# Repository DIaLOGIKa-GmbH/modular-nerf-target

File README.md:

# Nodular Nerf Target

A hex-based modular system to build custom nerf gun targets

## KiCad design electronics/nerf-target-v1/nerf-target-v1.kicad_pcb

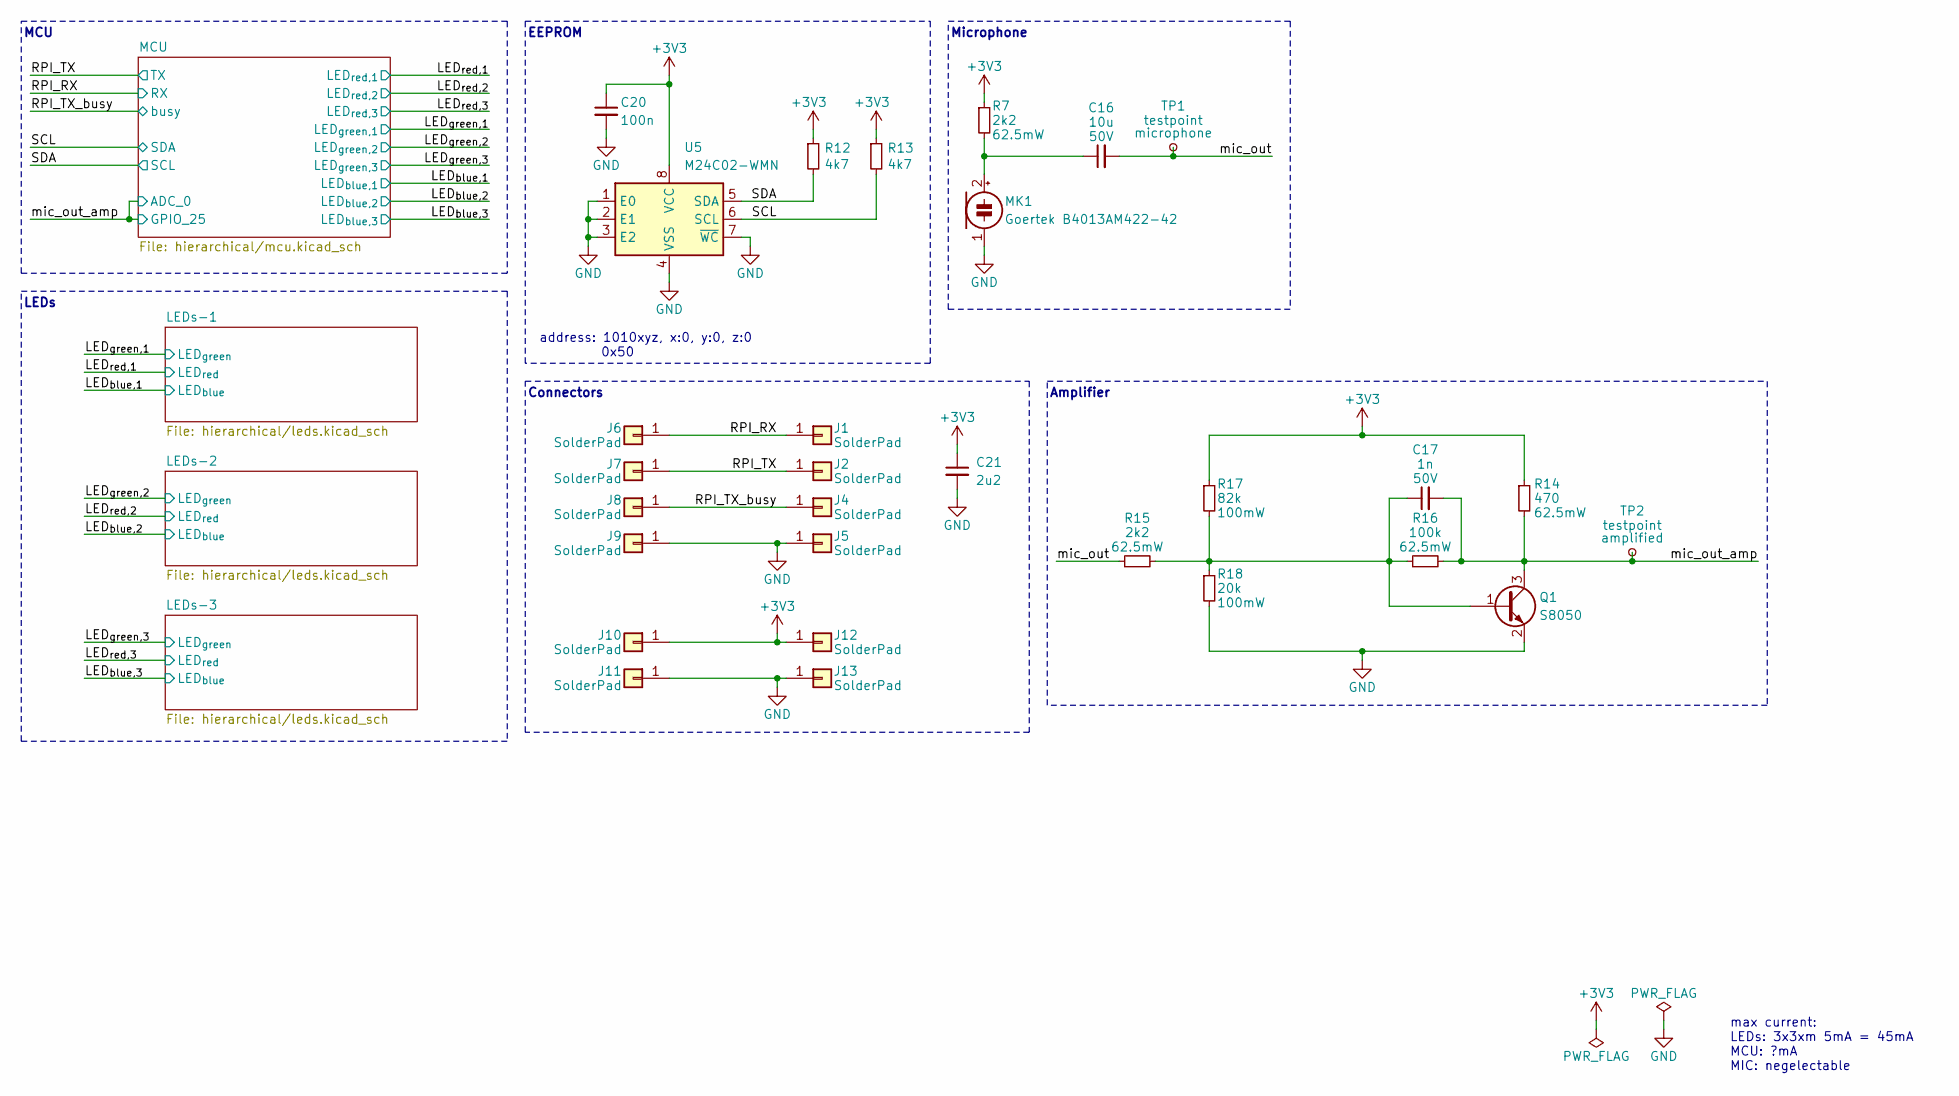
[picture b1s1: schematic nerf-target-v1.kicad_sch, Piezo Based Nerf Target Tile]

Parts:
C16: 10u; C_0805_2012Metric; Voltage 50V; LCSC Part # C440198
C17: 1n; C_0805_2012Metric; Voltage 50V; LCSC Part # C46653
C20: 100n; C_0402_1005Metric; LCSC Part # C1525
C21: 2u2; C_0603_1608Metric; JLC Part # C28323
J1, J2, J4, J5, J6, J7, J8, J9, J10, J11, J12, J13: SolderPad; solder_pad_1.2x2.5mm
MK1: Goertek B4013AM422-42; B4013AM422-42; LCSC Part # C233793
Q1: S8050; SOT-23; LCSC Part # C2146
R7, R15: 2k2; R_0402_1005Metric; LCSC Part # C25879
R12, R13: 4k7; R_0603_1608Metric; LCSC Part # C23162
R14: 470; R_0402_1005Metric; LCSC Part # C25117
R16: 100k; R_0603_1608Metric; LCSC Part # C25741
R17: 82k; R_0603_1608Metric; LCSC Part # C23254
R18: 20k; R_0603_1608Metric; LCSC Part # C4184
TP1, TP2: testpoint; TestPoint_Pad_D2.0mm
U5: M24C02-WMN; SOIC-8_3.9x4.9mm_P1.27mm; LCSC Part # C7562

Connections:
+3V3: C20.1, C21.1, J10.1, J12.1, R7.1, R12.1, R13.1, R14.1, R17.1, U5.8 (VCC); also elsewhere on the board
/RPI_RX: J1.1, J6.1; also elsewhere on the board
/RPI_TX: J2.1, J7.1; also elsewhere on the board
/RPI_TX_busy: J4.1, J8.1; also elsewhere on the board
/SCL: R13.2, U5.6 (SCL); also elsewhere on the board
/SDA: R12.2, U5.5 (SDA); also elsewhere on the board
/mic_out: C16.2, R15.1, TP1.1
/mic_out_amp: C17.2, Q1.3 (C), R14.2, R16.2, TP2.1; also elsewhere on the board
GND: C20.2, C21.2, J5.1, J9.1, J11.1, J13.1, MK1.1 (-), Q1.2 (E), R18.2, U5.1 (E0), U5.2 (E1), U5.3 (E2), U5.4 (VSS), U5.7 (~WC); also elsewhere on the board
unnamed: C16.1, MK1.2 (+), R7.2
unnamed: C17.1, Q1.1 (B), R15.2, R16.1, R17.2, R18.1

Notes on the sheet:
max current: LEDs: 3x3xm 5mA = 45mA MCU: ?mA MIC: negelectable
Microphone
Amplifier
MCU
Connectors
EEPROM
address: 1010xyz, x:0, y:0, z:0 0x50
LEDs

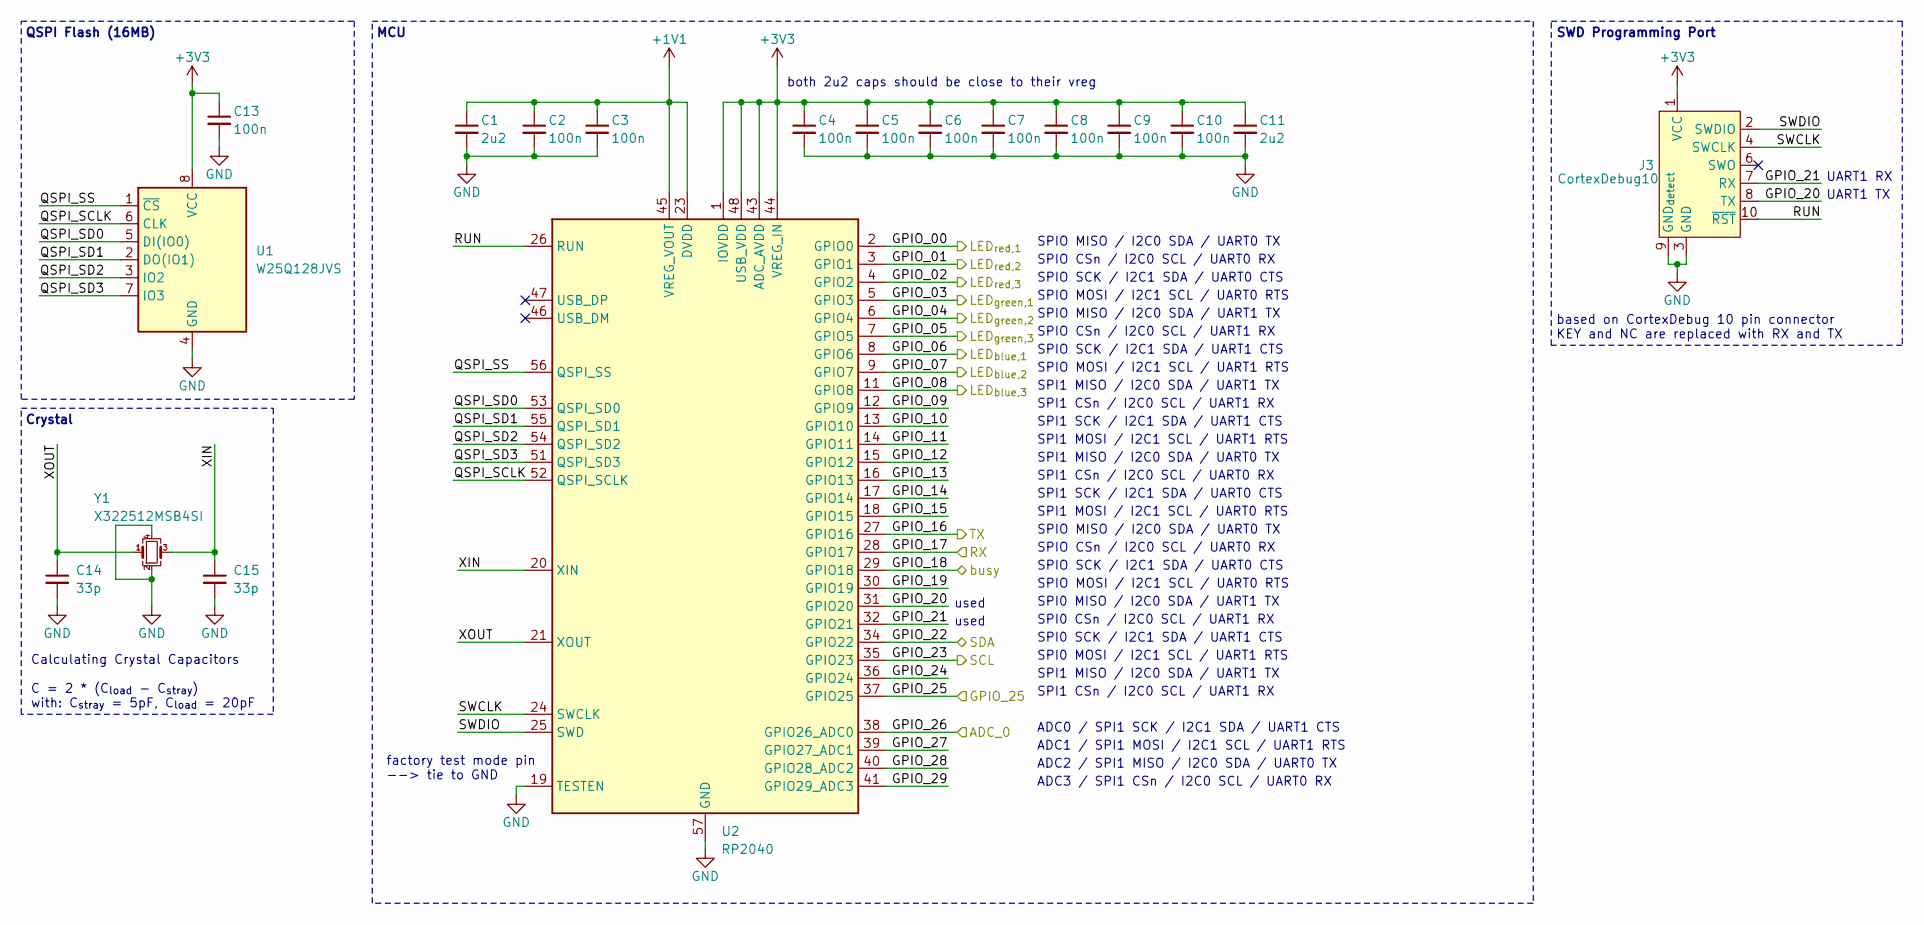
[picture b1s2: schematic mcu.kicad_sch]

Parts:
C1, C11: 2u2; C_0603_1608Metric; LCSC Part # C23630
C2, C3, C4, C5, C6, C7, C8, C9, C10, C13: 100n; C_0402_1005Metric; LCSC Part # C1525
C14, C15: 33p; C_0402_1005Metric; LCSC Part # C1562
J3: CortexDebug10; FTSH-105-01-F-DV-K; LCSC Part # C3975188
U1: W25Q128JVS; SOIC-8_5.275x5.275mm_P1.27mm; LCSC Part # C97521
U2: RP2040; QFN-56-1EP_7x7mm_P0.4mm_EP3.2x3.2mm; LCSC Part # C2040
Y1: X322512MSB4SI; Crystal_SMD_3225-4Pin_3.2x2.5mm; LCSC Part # C9002

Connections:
+1V1: C1.1, C2.1, C3.1, U2.23 (DVDD), U2.45 (VREG_VOUT), U2.50 (DVDD)
+3V3: C4.1, C5.1, C6.1, C7.1, C8.1, C9.1, C10.1, C11.1, C13.1, J3.1 (VCC), U1.8 (VCC), U2.1 (IOVDD), U2.10 (IOVDD), U2.22 (IOVDD), U2.33 (IOVDD), U2.42 (IOVDD), U2.43 (ADC_AVDD), U2.44 (VREG_IN), U2.48 (USB_VDD), U2.49 (IOVDD); also elsewhere on the board
/LED_{blue,1}: U2.8 (GPIO6); also elsewhere on the board
/LED_{blue,2}: U2.9 (GPIO7); also elsewhere on the board
/LED_{blue,3}: U2.11 (GPIO8); also elsewhere on the board
/LED_{green,1}: U2.5 (GPIO3); also elsewhere on the board
/LED_{green,2}: U2.6 (GPIO4); also elsewhere on the board
/LED_{green,3}: U2.7 (GPIO5); also elsewhere on the board
/LED_{red,1}: U2.2 (GPIO0); also elsewhere on the board
/LED_{red,2}: U2.3 (GPIO1); also elsewhere on the board
/LED_{red,3}: U2.4 (GPIO2); also elsewhere on the board
/MCU/GPIO_09: U2.12 (GPIO9)
/MCU/GPIO_10: U2.13 (GPIO10)
/MCU/GPIO_11: U2.14 (GPIO11)
/MCU/GPIO_12: U2.15 (GPIO12)
/MCU/GPIO_13: U2.16 (GPIO13)
/MCU/GPIO_14: U2.17 (GPIO14)
/MCU/GPIO_15: U2.18 (GPIO15)
/MCU/GPIO_19: U2.30 (GPIO19)
/MCU/GPIO_20: J3.8 (TX), U2.31 (GPIO20)
/MCU/GPIO_21: J3.7 (RX), U2.32 (GPIO21)
/MCU/GPIO_24: U2.36 (GPIO24)
/MCU/GPIO_27: U2.39 (GPIO27_ADC1)
/MCU/GPIO_28: U2.40 (GPIO28_ADC2)
/MCU/GPIO_29: U2.41 (GPIO29_ADC3)
/MCU/QSPI_SCLK: U1.6 (CLK), U2.52 (QSPI_SCLK)
/MCU/QSPI_SD0: U1.5 (DI(IO0)), U2.53 (QSPI_SD0)
/MCU/QSPI_SD1: U1.2 (DO(IO1)), U2.55 (QSPI_SD1)
/MCU/QSPI_SD2: U1.3 (IO2), U2.54 (QSPI_SD2)
/MCU/QSPI_SD3: U1.7 (IO3), U2.51 (QSPI_SD3)
/MCU/QSPI_SS: U1.1 (~CS), U2.56 (QSPI_SS)
/MCU/RUN: J3.10 (~RST), U2.26 (RUN)
/MCU/SWCLK: J3.4 (SWCLK), U2.24 (SWCLK)
/MCU/SWDIO: J3.2 (SWDIO), U2.25 (SWD)
/MCU/XIN: C15.1, U2.20 (XIN), Y1.3
/MCU/XOUT: C14.1, U2.21 (XOUT), Y1.1
/RPI_RX: U2.28 (GPIO17); also elsewhere on the board
/RPI_TX: U2.27 (GPIO16); also elsewhere on the board
/RPI_TX_busy: U2.29 (GPIO18); also elsewhere on the board
/SCL: U2.34 (GPIO22); also elsewhere on the board
/SDA: U2.35 (GPIO23); also elsewhere on the board
/mic_out_amp: U2.37 (GPIO25), U2.38 (GPIO26_ADC0); also elsewhere on the board
GND: C1.2, C2.2, C3.2, C4.2, C5.2, C6.2, C7.2, C8.2, C9.2, C10.2, C11.2, C13.2, C14.2, C15.2, J3.3 (GND), J3.5 (GND), J3.9 (GND_{detect}), U1.4 (GND), U2.19 (TESTEN), U2.57 (GND), Y1.2, Y1.4; also elsewhere on the board

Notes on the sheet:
SPI1 SCK / I2C1 SDA / UART0 CTS
SPIO CSn / I2C0 SCL / UART1 RX
SPI1 MISO / I2C0 SDA / UART1 TX
SPI1 CSn / I2C0 SCL / UART0 RX
SPI0 SCK / I2C1 SDA / UART1 CTS
SPI0 MOSI / I2C1 SCL / UART1 RTS
SPIO MOSI / I2C1 SCL / UART1 RTS
SPIO CSn / I2C0 SCL / UART0 RX
SPI1 SCK / I2C1 SDA / UART1 CTS
SPIO MOSI / I2C1 SCL / UART0 RTS
SPIO SCK / I2C1 SDA / UART0 CTS
ADC3 / SPI1 CSn / I2C0 SCL / UART0 RX
SPI1 MOSI / I2C1 SCL / UART0 RTS
SPI1 CSn / I2C0 SCL / UART1 RX
ADC0 / SPI1 SCK / I2C1 SDA / UART1 CTS
SPI0 MISO / I2C0 SDA / UART1 TX
based on CortexDebug 10 pin connector KEY and NC are replaced with RX and TX
UART1 RX
SWD Programming Port
SPI1 MOSI / I2C1 SCL / UART1 RTS
Crystal
SPIO SCK / I2C1 SDA / UART1 CTS
SPI1 MISO / I2C0 SDA / UART0 TX
Calculating Crystal Capacitors C = 2 * (C_{load} - C_{stray}) with: C_{stray} = 5pF, C_{load} = 20pF
SPIO MISO / I2C0 SDA / UART0 TX
used
SPIO MISO / I2C0 SDA / UART1 TX
factory test mode pin --> tie to GND
QSPI Flash (16MB)
both 2u2 caps should be close to their vreg
UART1 TX
ADC2 / SPI1 MISO / I2C0 SDA / UART0 TX
SPI0 CSn / I2C0 SCL / UART1 RX
MCU
ADC1 / SPI1 MOSI / I2C1 SCL / UART1 RTS

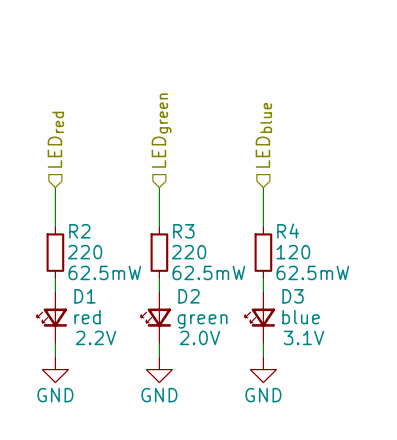
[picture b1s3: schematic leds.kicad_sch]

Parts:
D1: red; LED_0603_1608Metric; Voltage 2.2V; LCSC Part # C2286
D2: green; LED_0603_1608Metric; Voltage 2.0V; LCSC Part # C84264
D3: blue; LED_0603_1608Metric; Voltage 3.1V; LCSC Part # C965807
R2, R3: 220; R_0402_1005Metric; LCSC Part # C25091
R4: 120; R_0402_1005Metric; LCSC Part # C25079

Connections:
/LED_{blue,1}: R4.1; also elsewhere on the board
/LED_{green,1}: R3.1; also elsewhere on the board
/LED_{red,1}: R2.1; also elsewhere on the board
GND: D1.1 (K), D2.1 (K), D3.1 (K); also elsewhere on the board
unnamed: D1.2 (A), R2.2
unnamed: D2.2 (A), R3.2
unnamed: D3.2 (A), R4.2

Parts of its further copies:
D4, D7: red; LED_0603_1608Metric; Voltage 2.2V; LCSC Part # C2286
D5, D8: green; LED_0603_1608Metric; Voltage 2.0V; LCSC Part # C84264
D6, D9: blue; LED_0603_1608Metric; Voltage 3.1V; LCSC Part # C965807
R5, R6, R9, R10: 220; R_0402_1005Metric; LCSC Part # C25091
R8, R11: 120; R_0402_1005Metric; LCSC Part # C25079

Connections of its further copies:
/LED_{blue,2}: R8.1; also elsewhere on the board
/LED_{blue,3}: R11.1; also elsewhere on the board
/LED_{green,2}: R6.1; also elsewhere on the board
/LED_{green,3}: R10.1; also elsewhere on the board
/LED_{red,2}: R5.1; also elsewhere on the board
/LED_{red,3}: R9.1; also elsewhere on the board
GND: D4.1 (K), D5.1 (K), D6.1 (K), D7.1 (K), D8.1 (K), D9.1 (K); also elsewhere on the board
unnamed: D4.2 (A), R5.2
unnamed: D5.2 (A), R6.2
unnamed: D6.2 (A), R8.2
unnamed: D7.2 (A), R9.2
unnamed: D8.2 (A), R10.2
unnamed: D9.2 (A), R11.2

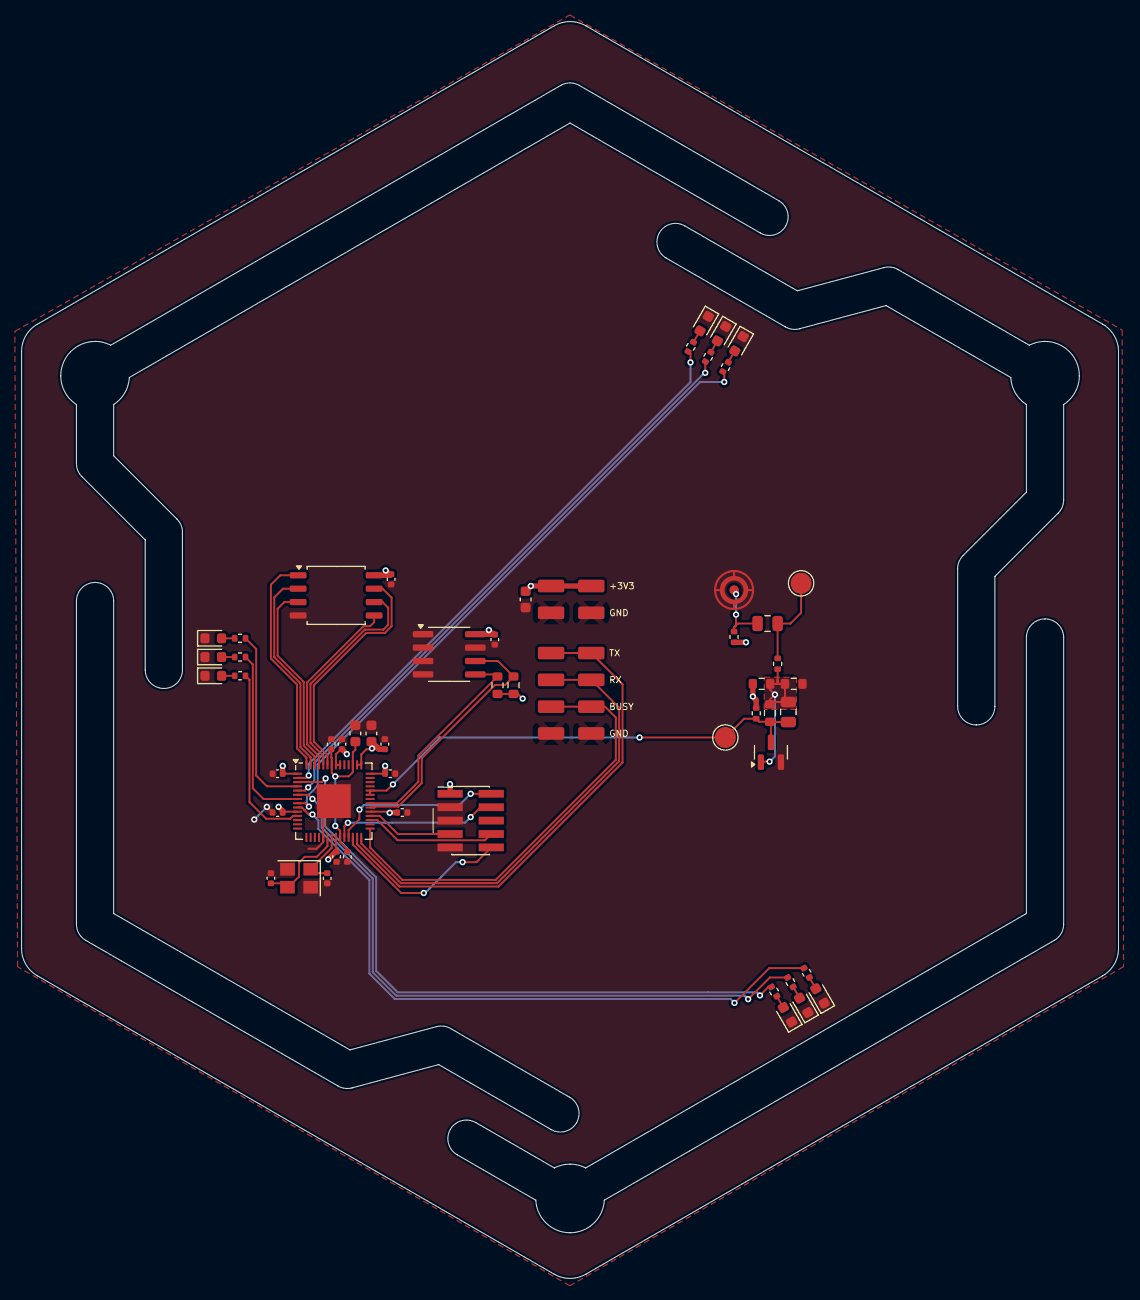
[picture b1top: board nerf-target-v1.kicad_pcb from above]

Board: 2 copper layers, 103.9 x 119.1 mm, 65 parts (0 on the bottom side), 43 nets.

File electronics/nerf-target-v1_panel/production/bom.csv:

Designator,Footprint,Quantity,Value,LCSC Part #
"C1_4, C1_3, C1_2, C1, C11_4, C11_3, C11_2, C11, C21_4, C21_3, C21_2, C21",0603,12,2u2,C23630
"C10_4, C10_3, C10_2, C10, C13_4, C13_3, C13_2, C13, C2_4, C2_3, C2_2, C2, C20_4, C20_3, C20_2, C20, C3_4, C3_3, C3_2, C3, C4_4, C4_3, C4_2, C4, C5_4, C5_3, C5_2, C5, C6_4, C6_3, C6_2, C6, C7_4, C7_3, C7_2, C7, C8_4, C8_3, C8_2, C8, C9_4, C9_3, C9_2, C9",0402,44,100n,C1525
"C14_4, C14_3, C14_2, C14, C15_4, C15_3, C15_2, C15",0402,8,33p,C1562
"C16_4, C16_3, C16_2, C16",0805,4,10u,C440198
"C17_4, C17_3, C17_2, C17",0805,4,1n,C46653
"D1_4, D1_3, D1_2, D1, D4_4, D4_3, D4_2, D4, D7_4, D7_3, D7_2, D7",0603,12,red,C2286
"D2_4, D2_3, D2_2, D2, D5_4, D5_3, D5_2, D5, D8_4, D8_3, D8_2, D8",0603,12,green,C84264
"D3_4, D3_3, D3_2, D3, D6_4, D6_3, D6_2, D6, D9_4, D9_3, D9_2, D9",0603,12,blue,C965807
"J3_4, J3_3, J3_2, J3",FTSH-105-01-F-DV-K,4,CortexDebug10,C3975188
"KiKit_FID_B_1, KiKit_FID_B_2, KiKit_FID_B_3, KiKit_FID_T_1, KiKit_FID_T_2, KiKit_FID_T_3",Fiducial,6,Fiducial,
"KiKit_MB_10_2, KiKit_MB_10_3, KiKit_MB_10_4, KiKit_MB_11_1, KiKit_MB_11_2, KiKit_MB_11_3, KiKit_MB_11_4, KiKit_MB_12_1, KiKit_MB_12_2, KiKit_MB_12_3, KiKit_MB_12_4, KiKit_MB_13_1, KiKit_MB_13_2, KiKit_MB_13_3, KiKit_MB_13_4, KiKit_MB_14_1, KiKit_MB_14_2, KiKit_MB_14_3, KiKit_MB_14_4, KiKit_MB_15_2, KiKit_MB_15_3, KiKit_MB_15_4, KiKit_MB_16_1, KiKit_MB_16_2, KiKit_MB_16_3, KiKit_MB_16_4, KiKit_MB_17_1, KiKit_MB_17_2, KiKit_MB_17_3, KiKit_MB_17_4, KiKit_MB_18_1, KiKit_MB_18_2, KiKit_MB_18_3, KiKit_MB_18_4, KiKit_MB_19_1, KiKit_MB_19_2, KiKit_MB_19_3, KiKit_MB_19_4, KiKit_MB_1_1, KiKit_MB_1_2, KiKit_MB_1_3, KiKit_MB_1_4, KiKit_MB_20_2, KiKit_MB_20_3, KiKit_MB_20_4, KiKit_MB_2_1, KiKit_MB_2_2, KiKit_MB_2_3, KiKit_MB_2_4, KiKit_MB_3_1, KiKit_MB_3_2, KiKit_MB_3_3, KiKit_MB_3_4, KiKit_MB_4_1, KiKit_MB_4_2, KiKit_MB_4_3, KiKit_MB_4_4, KiKit_MB_5_2, KiKit_MB_5_3, KiKit_MB_5_4, KiKit_MB_6_1, KiKit_MB_6_2, KiKit_MB_6_3, KiKit_MB_6_4, KiKit_MB_7_1, KiKit_MB_7_2, KiKit_MB_7_3, KiKit_MB_7_4, KiKit_MB_8_1, KiKit_MB_8_2, KiKit_MB_8_3, KiKit_MB_8_4, KiKit_MB_9_1, KiKit_MB_9_2, KiKit_MB_9_3, KiKit_MB_9_4, KiKit_TO_1, KiKit_TO_2, KiKit_TO_3, KiKit_TO_4",NPTH,80,NPTH,
"MK1_4, MK1_3, MK1_2, MK1",B4013AM422-42,4,Goertek B4013AM422-42,C233793
"Q1_4, Q1_3, Q1_2, Q1",SOT-23,4,S8050,C2146
"R10_4, R10_3, R10_2, R10, R2_4, R2_3, R2_2, R2, R3_4, R3_3, R3_2, R3, R5_4, R5_3, R5_2, R5, R6_4, R6_3, R6_2, R6, R9_4, R9_3, R9_2, R9",0402,24,220,C25091
"R11_4, R11_3, R11_2, R11, R4_4, R4_3, R4_2, R4, R8_4, R8_3, R8_2, R8",0402,12,120,C25079
"R12_4, R12_3, R12_2, R12, R13_4, R13_3, R13_2, R13",0603,8,4k7,C23162
"R14_4, R14_3, R14_2, R14",0402,4,470,C25117
"R15_4, R15_3, R15_2, R15, R7_4, R7_3, R7_2, R7",0402,8,2k2,C25879
"R16_4, R16_3, R16_2, R16",0603,4,100k,C25741
"R17_4, R17_3, R17_2, R17",0603,4,82k,C23254
"R18_4, R18_3, R18_2, R18",0603,4,20k,C4184
"U1_4, U1_3, U1_2, U1",SOIC-8_5.275x5.275mm_P1.27mm,4,W25Q128JVS,C97521
"U2_4, U2_3, U2_2, U2",QFN-56-1EP_7x7mm_P0.4mm_EP3.2x3.2mm,4,RP2040,C2040
"U5_4, U5_3, U5_2, U5",SOIC-8_3.9x4.9mm_P1.27mm,4,M24C02-WMN,C7562
"Y1_4, Y1_3, Y1_2, Y1",Crystal_SMD_3225-4Pin_3.2x2.5mm,4,X322512MSB4SI,C9002

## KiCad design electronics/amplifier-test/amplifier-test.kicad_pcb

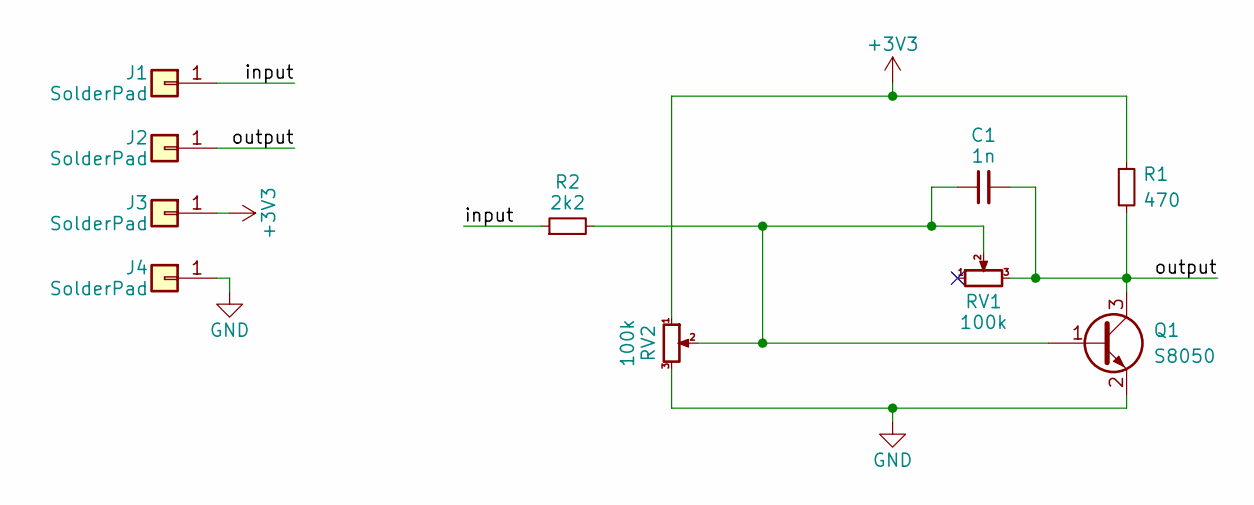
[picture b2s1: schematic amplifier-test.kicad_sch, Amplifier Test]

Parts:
C1: 1n; C_0805_2012Metric; LCSC Part # C46653
J1, J2, J3, J4: SolderPad; solder_connector
Q1: S8050; SOT-23; LCSC Part # C2146
R1: 470; R_0805_2012Metric; LCSC Part # C17710
R2: 2k2; R_0805_2012Metric; LCSC Part # C17520
RV1, RV2: 100k; Potentiometer_Bourns_3296Y_Vertical; LCSC Part # C780118

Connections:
+3V3: J3.1, R1.1, RV2.1
/input: J1.1, R2.1
/output: C1.2, J2.1, Q1.3 (C), R1.2, RV1.3
GND: J4.1, Q1.2 (E), RV2.3
unnamed: C1.1, Q1.1 (B), R2.2, RV1.2, RV2.2

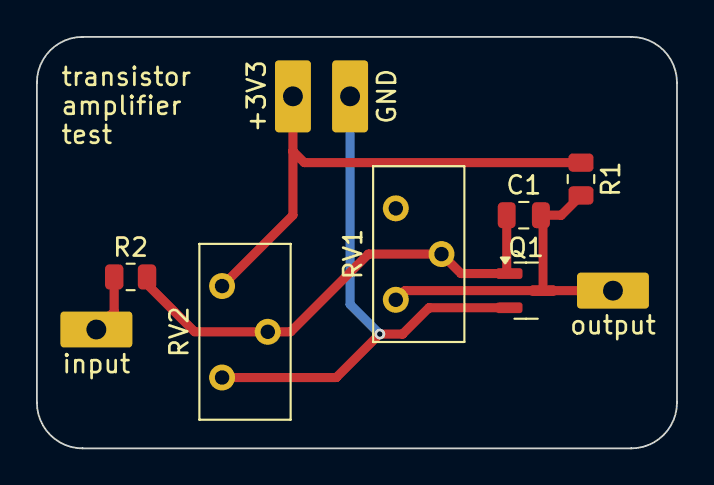
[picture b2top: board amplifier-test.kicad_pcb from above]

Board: 2 copper layers, 35.6 x 22.9 mm, 10 parts (0 on the bottom side), 5 nets.

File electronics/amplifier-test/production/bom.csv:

Designator,Footprint,Quantity,Value,LCSC Part #
C1,0805,1,1n,C46653
Q1,SOT-23,1,S8050,C2146
R1,0805,1,470,C17710
R2,0805,1,2k2,C17520
"RV1, RV2",Potentiometer_Bourns_3296Y_Vertical,2,100k,C780118

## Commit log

2024-04-06 set up project
2024-04-06 microphone circuit
2024-04-10 finished prototype
2024-04-24 switched part numbers
2024-04-24 added production files
2024-05-03 added amplifier simulation files
2024-05-26 revised v1.0
2024-05-27 finished board; production files
2024-05-28 3D model files
2024-06-10 REACT Frontend Initial Commit
2024-06-16 UI: New init procedure
2024-06-17 Scoreboard wip
2024-06-18 Scoreboard speichert und updated
2024-06-19 idMapping aus Datenbank laden
2024-06-19 UI updates
2024-06-20 Websocket Fix, UI Updates
2024-06-21 HandleHitOnClick
